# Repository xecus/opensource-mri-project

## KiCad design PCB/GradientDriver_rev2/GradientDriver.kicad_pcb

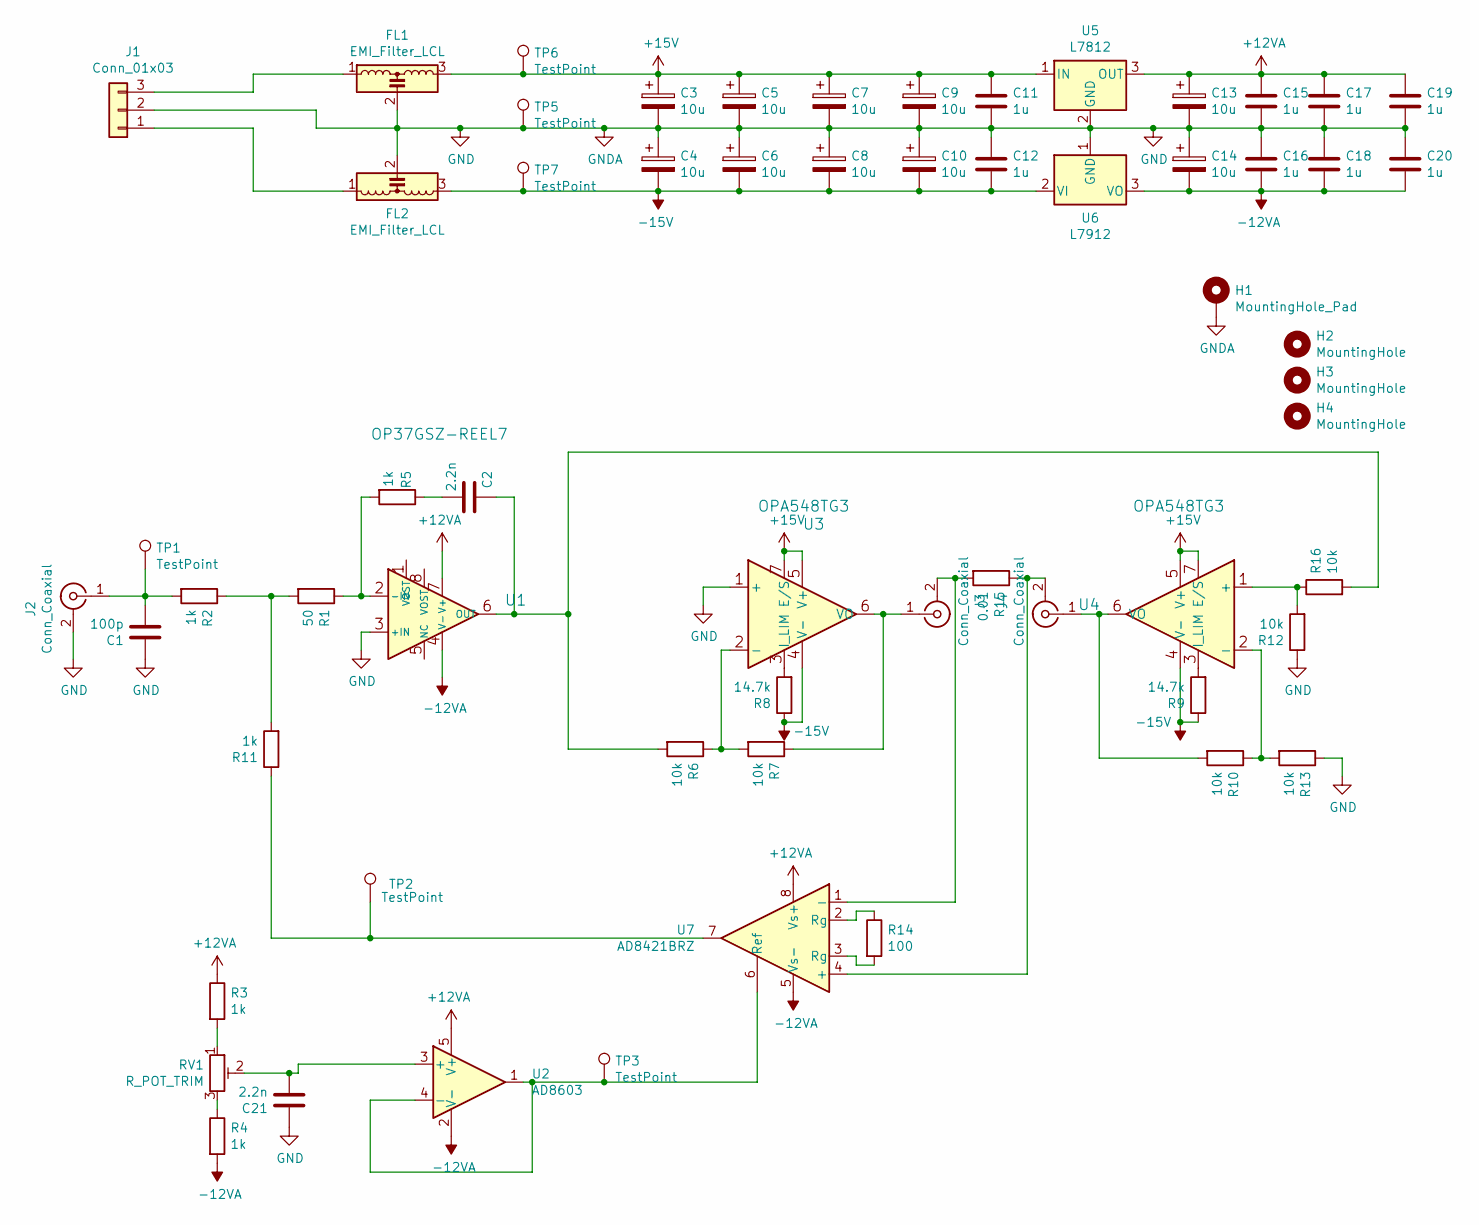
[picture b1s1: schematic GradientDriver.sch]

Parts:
C1: 100p; C_0603_1608Metric_Pad1.05x0.95mm_HandSolder
C2, C21: 2.2n; C_0603_1608Metric_Pad1.05x0.95mm_HandSolder
C3, C4, C5, C6, C7, C8, C9, C10, C13, C14: 10u; C_Elec_5x5.8
C11, C12, C15, C16, C17, C18, C19, C20: 1u; C_0603_1608Metric_Pad1.05x0.95mm_HandSolder
FL1, FL2: EMI_Filter_LCL; EMI_Filter_2606
H1: MountingHole_Pad; MountingHole_3.2mm_M3_Pad_Via
H2, H3, H4: MountingHole; MountingHole_3.2mm_M3_Pad_Via
J1: Conn_01x03; JST_XH_S3B-XH-A-1_1x03_P2.50mm_Horizontal
J2, J3, J4: Conn_Coaxial; SMA_Samtec_SMA-J-P-X-ST-EM1_EdgeMount
R1: 50; R_0603_1608Metric_Pad1.05x0.95mm_HandSolder
R2, R3, R4, R5, R11: 1k; R_0603_1608Metric_Pad1.05x0.95mm_HandSolder
R6, R7, R10, R12, R13, R16: 10k; R_0603_1608Metric_Pad1.05x0.95mm_HandSolder
R8, R9: 14.7k; R_0603_1608Metric_Pad1.05x0.95mm_HandSolder
R14: 100; R_0603_1608Metric_Pad1.05x0.95mm_HandSolder
R15: 0.01; R_2512_6332Metric_Pad1.52x3.35mm_HandSolder
RV1: R_POT_TRIM; Potentiometer_Bourns_3269W_Vertical
TP1, TP2, TP3, TP5, TP6, TP7: TestPoint; HK-1-G
U1: OP37GSZ-REEL7; SSOP-8_3.9x5.05mm_P1.27mm
U2: AD8603; TSOT-23-5
U3, U4: OPA548TG3
U5: L7812; TO-252-3_TabPin4
U6: L7912; TO-252-3_TabPin4
U7: AD8421BRZ; SOIC-8-1EP_3.9x4.9mm_P1.27mm_EP2.29x3mm

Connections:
+12VA: C13.1, C15.1, C17.1, C19.1, R3.1, U1.7 (V+), U2.5 (V+), U5.3 (OUT), U7.8 (Vs+)
+15V: C3.1, C5.1, C7.1, C9.1, C11.1, FL1.3, TP6.1, U3.5 (V+), U3.7 (E/S), U4.5 (V+), U4.7 (E/S), U5.1 (IN)
-12VA: C14.2, C16.2, C18.2, C20.2, R4.2, U1.4 (V-), U2.2 (V-), U6.3 (VO), U7.5 (Vs-)
-15V: C4.2, C6.2, C8.2, C10.2, C12.2, FL2.3, R8.1, R9.1, TP7.1, U3.4 (V-), U4.4 (V-), U6.2 (VI), U6.4
GND: C1.1, C3.2, C4.1, C5.2, C6.1, C7.2, C8.1, C9.2, C10.1, C11.2, C12.1, C13.2, C14.1, C15.2, C16.1, C17.2, C18.1, C19.2, C20.1, C21.1, FL1.2, FL2.2, H1.1, J1.2, J2.2 (Ext), R12.1, R13.1, TP5.1, U1.3 (+IN), U3.1 (+), U5.2 (GND), U6.1 (GND)
unnamed: C1.2, J2.1 (In), R2.2, TP1.1
unnamed: C2.1, R6.2, R16.2, U1.6 (OUT)
unnamed: C2.2, R5.1
unnamed: C21.2, RV1.2, U2.3 (+)
unnamed: FL1.1, J1.3
unnamed: FL2.1, J1.1
unnamed: J3.1 (In), R7.1, U3.6 (VO)
unnamed: J3.2 (Ext), R15.2, U7.1 (-)
unnamed: J4.1 (In), R10.2, U4.6 (VO)
unnamed: J4.2 (Ext), R15.1, U7.4 (+)
unnamed: R1.1, R5.2, U1.2 (-IN)
unnamed: R1.2, R2.1, R11.2
unnamed: R3.2, RV1.1
unnamed: R4.1, RV1.3
unnamed: R6.1, R7.2, U3.2 (-)
unnamed: R8.2, U3.3 (I_LIM)
unnamed: R9.2, U4.3 (I_LIM)
unnamed: R10.1, R13.2, U4.2 (-)
unnamed: R11.1, TP2.1, U7.7
unnamed: R12.2, R16.1, U4.1 (+)
unnamed: R14.1, U7.2 (Rg)
unnamed: R14.2, U7.3 (Rg)
unnamed: TP3.1, U2.1, U2.4 (-), U7.6 (Ref)

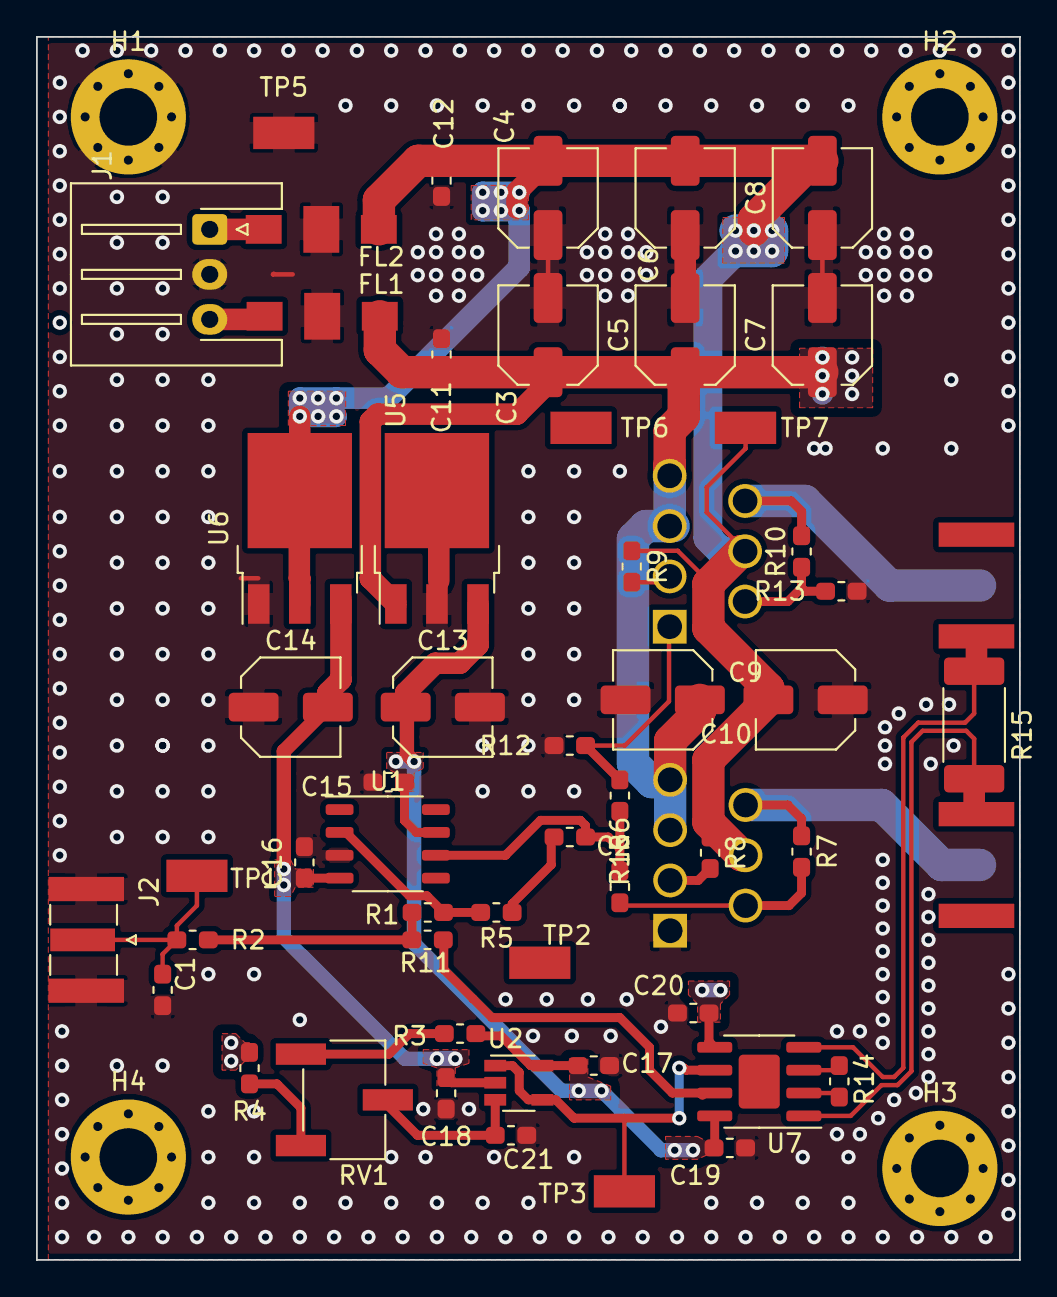
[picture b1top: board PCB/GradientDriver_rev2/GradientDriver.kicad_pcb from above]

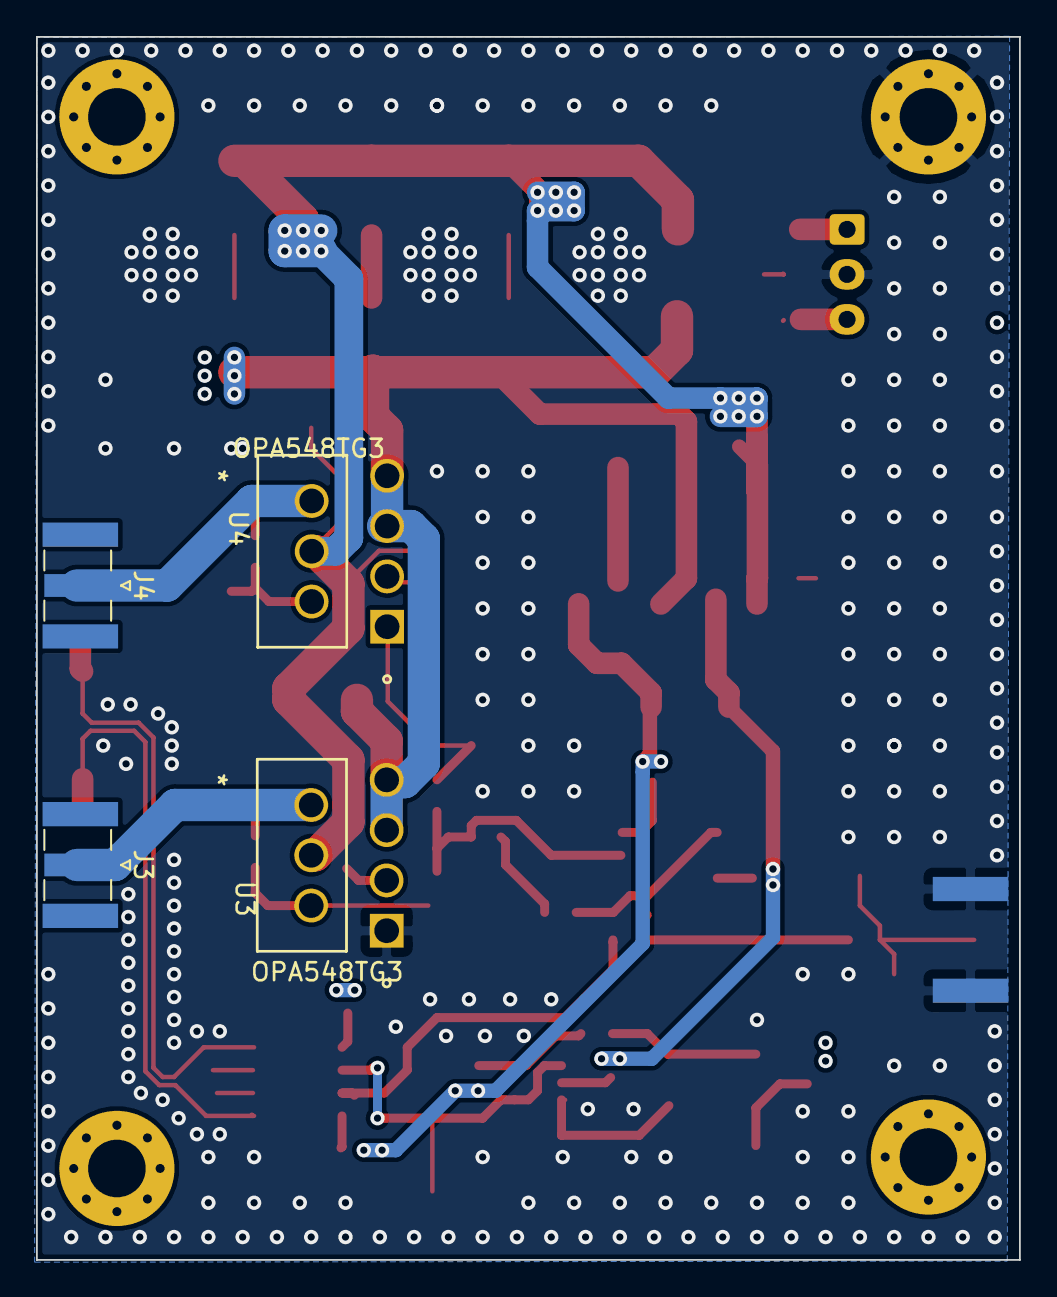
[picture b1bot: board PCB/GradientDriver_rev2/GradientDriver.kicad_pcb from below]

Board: 4 copper layers, 54.6 x 67.9 mm, 61 parts (4 on the bottom side), 28 nets.

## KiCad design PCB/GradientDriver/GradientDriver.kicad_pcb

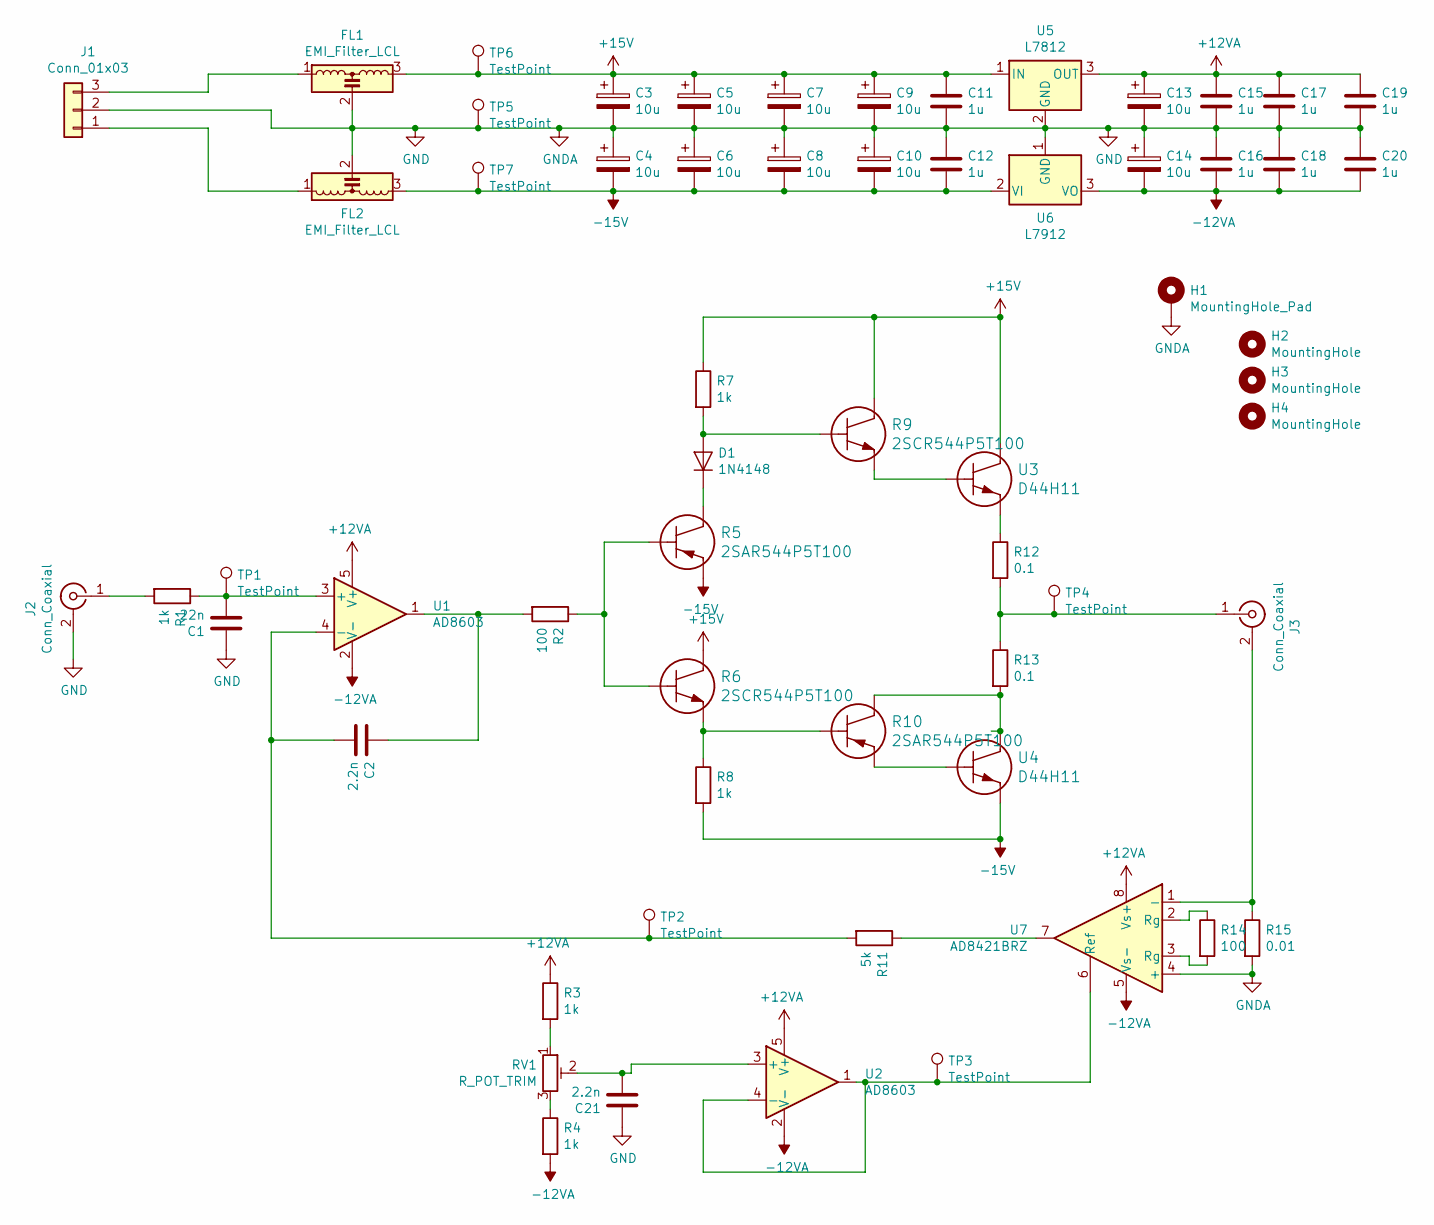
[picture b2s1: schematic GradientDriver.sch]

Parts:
C1: 22n; C_0603_1608Metric_Pad1.05x0.95mm_HandSolder
C2, C21: 2.2n; C_0603_1608Metric_Pad1.05x0.95mm_HandSolder
C3, C4, C5, C6, C7, C8, C9, C10, C13, C14: 10u; C_Elec_5x5.8
C11, C12, C15, C16, C17, C18, C19, C20: 1u; C_0603_1608Metric_Pad1.05x0.95mm_HandSolder
D1: 1N4148; D_SOD-323_HandSoldering
FL1, FL2: EMI_Filter_LCL; EMI_Filter_2606
H1: MountingHole_Pad; MountingHole_3.2mm_M3_Pad_Via
H2, H3, H4: MountingHole; MountingHole_3.2mm_M3_Pad_Via
J1: Conn_01x03; JST_XH_S3B-XH-A-1_1x03_P2.50mm_Horizontal
J2, J3: Conn_Coaxial; SMA_Samtec_SMA-J-P-X-ST-EM1_EdgeMount
R1, R3, R4, R7, R8: 1k; R_0603_1608Metric_Pad1.05x0.95mm_HandSolder
R2, R14: 100; R_0603_1608Metric_Pad1.05x0.95mm_HandSolder
R5, R10: 2SAR544P5T100; SOT-89-3_Handsoldering
R6, R9: 2SCR544P5T100; SOT-89-3_Handsoldering
R11: 5k; R_0603_1608Metric_Pad1.05x0.95mm_HandSolder
R12, R13: 0.1; TLRH3APTTER100F
R15: 0.01; R_2512_6332Metric_Pad1.52x3.35mm_HandSolder
RV1: R_POT_TRIM; Potentiometer_Bourns_3269W_Vertical
TP1, TP2, TP3, TP4, TP5, TP6, TP7: TestPoint; HK-1-G
U1, U2: AD8603; TSOT-23-5
U3, U4: D44H11
U5: L7812; TO-252-3_TabPin4
U6: L7912; TO-252-3_TabPin4
U7: AD8421BRZ; SOIC-8-1EP_3.9x4.9mm_P1.27mm_EP2.29x3mm

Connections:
+12VA: C13.1, C15.1, C17.1, C19.1, R3.1, U1.5 (V+), U2.5 (V+), U5.3 (OUT), U7.8 (Vs+)
+15V: C3.1, C5.1, C7.1, C9.1, C11.1, FL1.3, R6.2, R7.1, R9.2, TP6.1, U3.2 (C), U5.1 (IN)
-12VA: C14.2, C16.2, C18.2, C20.2, R4.2, U1.2 (V-), U2.2 (V-), U6.3 (VO), U7.5 (Vs-)
-15V: C4.2, C6.2, C8.2, C10.2, C12.2, FL2.3, R5.3, R8.2, TP7.1, U4.3 (E), U6.2 (VI), U6.4
GND: C1.1, C3.2, C4.1, C5.2, C6.1, C7.2, C8.1, C9.2, C10.1, C11.2, C12.1, C13.2, C14.1, C15.2, C16.1, C17.2, C18.1, C19.2, C20.1, C21.1, FL1.2, FL2.2, H1.1, J1.2, J2.2 (Ext), R15.2, TP5.1, U5.2 (GND), U5.4, U6.1 (GND), U7.4 (+)
unnamed: C1.2, R1.1, TP1.1, U1.3 (+)
unnamed: C2.1, R2.2, U1.1
unnamed: C2.2, R11.2, TP2.1, U1.4 (-)
unnamed: C21.2, RV1.2, U2.3 (+)
unnamed: D1.1 (K), R5.2
unnamed: D1.2 (A), R7.2, R9.1
unnamed: FL1.1, J1.3
unnamed: FL2.1, J1.1
unnamed: J2.1 (In), R1.2
unnamed: J3.1 (In), R12.2, R13.1, TP4.1
unnamed: J3.2 (Ext), R15.1, U7.1 (-)
unnamed: R2.1, R5.1, R6.1
unnamed: R3.2, RV1.1
unnamed: R4.1, RV1.3
unnamed: R9.3, U3.1 (B)
unnamed: R6.3, R8.1, R10.1
unnamed: R10.2, R13.2, U4.2 (C)
unnamed: R10.3, U4.1 (B)
unnamed: R11.1, U7.7
unnamed: R12.1, U3.3 (E)
unnamed: R14.1, U7.2 (Rg)
unnamed: R14.2, U7.3 (Rg)
unnamed: TP3.1, U2.1, U2.4 (-), U7.6 (Ref)

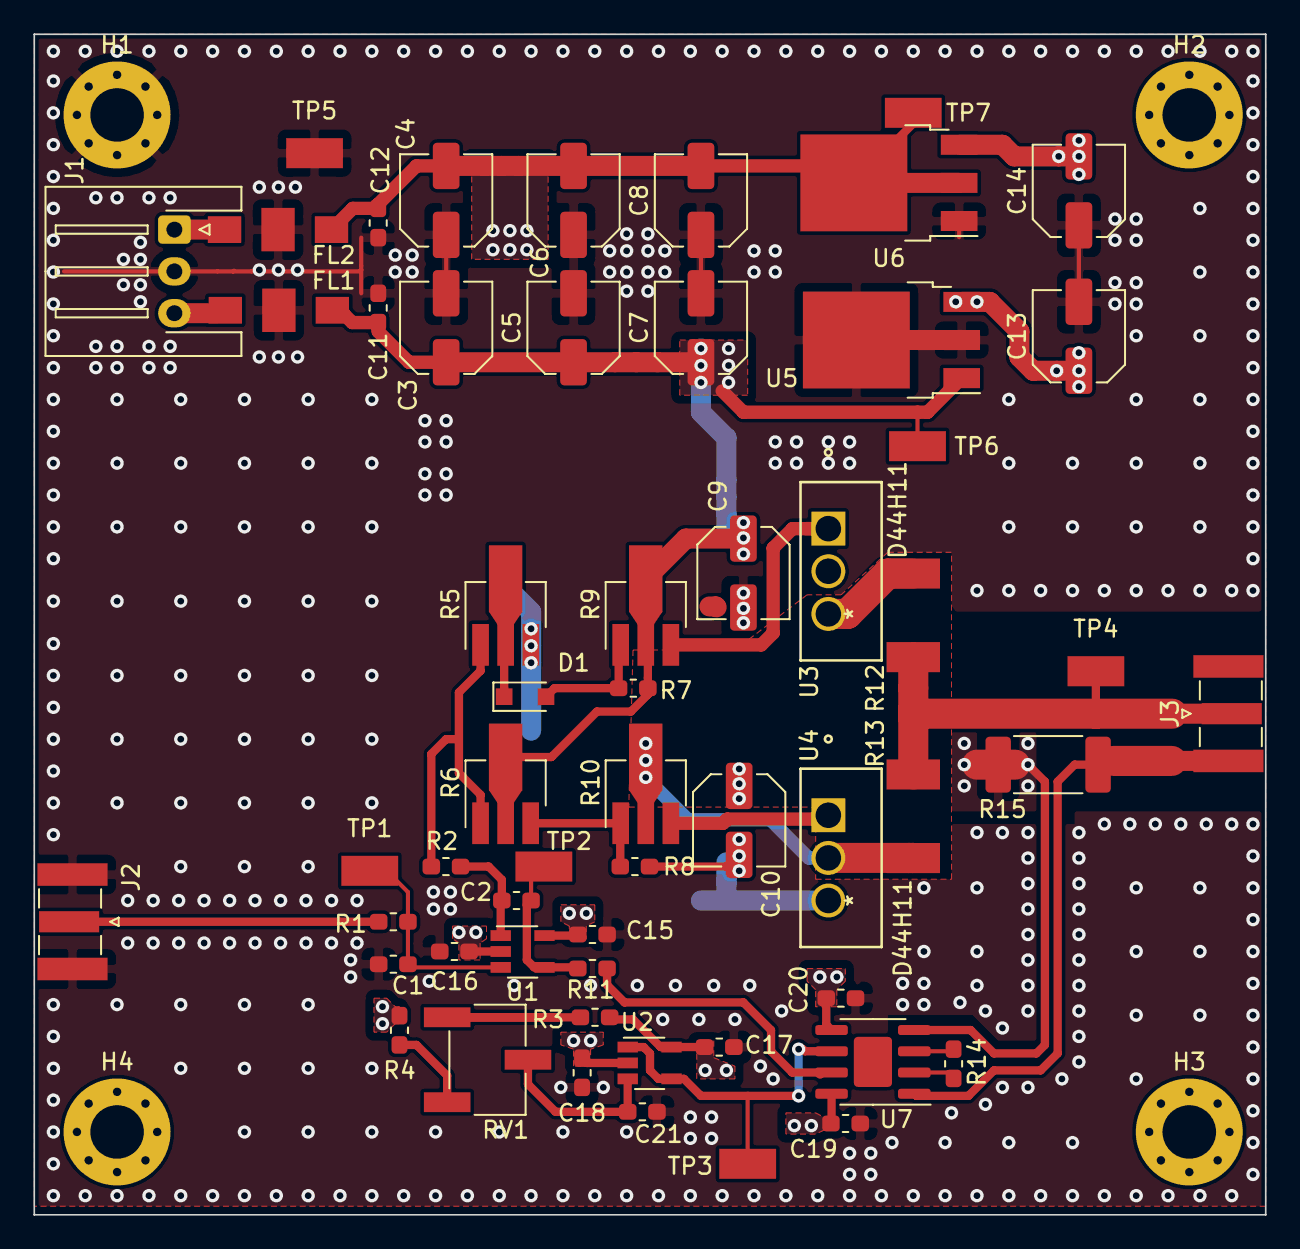
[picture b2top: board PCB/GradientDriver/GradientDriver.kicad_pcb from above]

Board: 4 copper layers, 73.7 x 70.6 mm, 61 parts (0 on the bottom side), 28 nets.

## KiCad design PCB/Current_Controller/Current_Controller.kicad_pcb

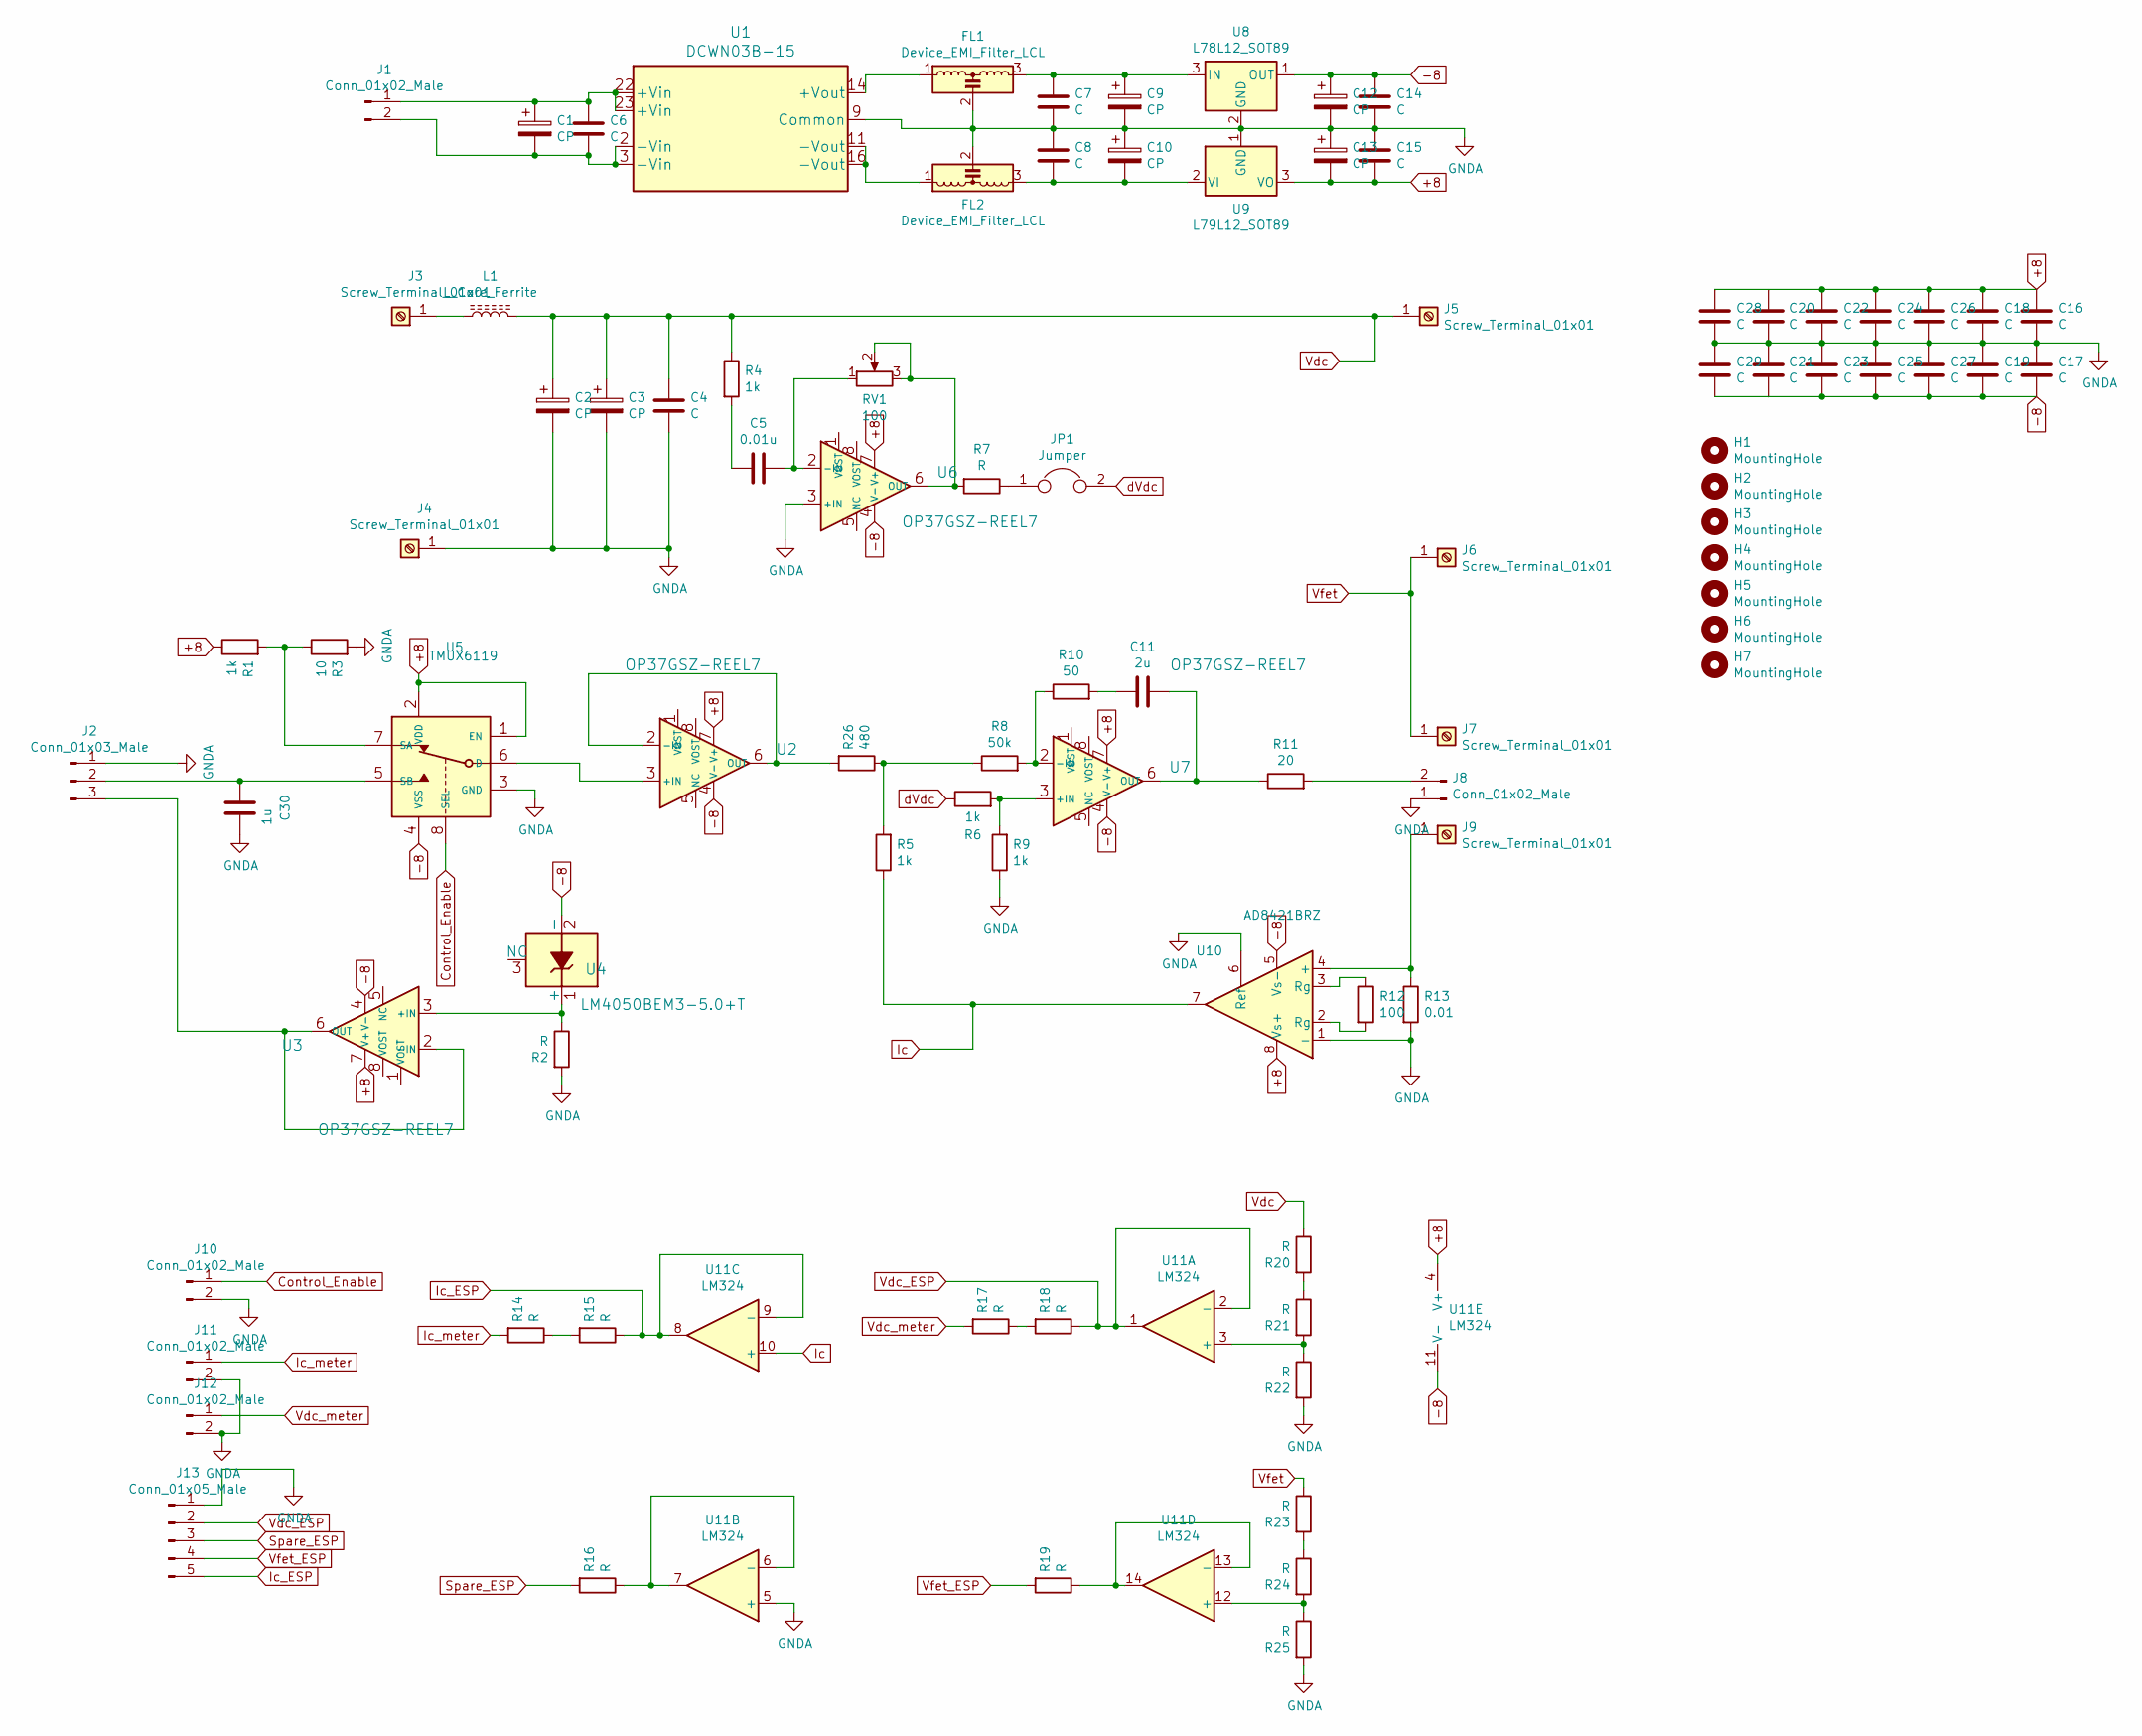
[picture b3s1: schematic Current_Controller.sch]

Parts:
C1, C9, C10, C12, C13: CP; CP_Elec_5x5.8
C2, C3: CP; CP_Radial_D30.0mm_P10.00mm_SnapIn
C4: C; C_Rect_L10.3mm_W5.7mm_P7.50mm_MKS4
C5: 0.01u; C_0603_1608Metric
C6, C7, C8, C14, C15, C16, C17, C18, C19, C20, C21, C22, C23, C24, C25, C26, C27, C28, C29: C; C_0603_1608Metric
C11: 2u; C_0603_1608Metric
C30: 1u; C_0603_1608Metric
FL1, FL2: Device_EMI_Filter_LCL; EMI_Filter_2606
H1, H2, H3, H4, H5, H6, H7: MountingHole; MountingHole_3.2mm_M3_Pad_Via
J1, J8, J10, J11, J12: Conn_01x02_Male; JST_XH_B2B-XH-AM_1x02_P2.50mm_Vertical
J2: Conn_01x03_Male; JST_XH_B3B-XH-AM_1x03_P2.50mm_Vertical
J3, J4, J5, J6, J7, J9: Screw_Terminal_01x01; keystone_7698
J13: Conn_01x05_Male; JST_XH_B5B-XH-AM_1x05_P2.50mm_Vertical
JP1: Jumper; PinHeader_1x02_P2.54mm_Vertical
L1: L_Core_Ferrite; L_250uH2
R1, R4, R5, R6, R9: 1k; R_0603_1608Metric
R2, R7, R14, R15, R16, R17, R18, R19, R20, R21, R22, R23, R24, R25: R; R_0603_1608Metric
R3: 10; R_0603_1608Metric
R8: 50k; R_0603_1608Metric
R10: 50; R_0603_1608Metric
R11: 20; R_0603_1608Metric
R12: 100; R_0603_1608Metric
R13: 0.01; GMR100HTBFA10L0
R26: 480; R_0603_1608Metric
RV1: 100; Potentiometer_Bourns_3269W_Vertical
U1: DCWN03B-15; DCWN03B-12
U2, U3, U6, U7: OP37GSZ-REEL7; SOIC-8_3.9x4.9mm_P1.27mm
U4: LM4050BEM3-5.0+T; LM4050QBEM3-8.2&slash_NOPB
U5: TMUX6119; SOT-23-8
U8: L78L12_SOT89; SOT-89-3
U9: L79L12_SOT89; SOT-89-3
U10: AD8421BRZ; SOIC-8_3.9x4.9mm_P1.27mm
U11: LM324; TSSOP-14_4.4x5mm_P0.65mm

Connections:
+8: C13.2, C15.1, C16.2, C18.2, C20.2, C22.2, C24.2, C26.2, C28.2, R1.1, U2.7 (V+), U3.7 (V+), U5.1 (EN), U5.2 (VDD), U6.7 (V+), U7.7 (V+), U9.3 (VO), U10.8 (Vs+), U11.4 (V+)
-8: C12.1, C14.2, C17.1, C19.1, C21.1, C23.1, C25.1, C27.1, C29.1, U2.4 (V-), U3.4 (V-), U4.2 (-), U5.4 (VSS), U6.4 (V-), U7.4 (V-), U8.1 (OUT), U10.5 (Vs-), U11.11 (V-)
Control_Enable: J10.1, U5.8 (SEL)
GNDA: C2.2, C3.2, C4.1, C7.1, C8.2, C9.2, C10.1, C12.2, C13.1, C14.1, C15.2, C16.1, C17.2, C18.1, C19.2, C20.1, C21.2, C22.1, C23.2, C24.1, C25.2, C26.1, C27.2, C28.1, C29.2, C30.1, FL1.2, FL2.2, J2.1, J4.1, J8.1, J10.2, J11.2, J12.2, J13.1, R2.2, R3.2, R9.1, R13.2, R22.2, R25.2, U1.9 (Common), U5.3 (GND), U6.3 (+IN), U8.2 (GND), U9.1 (GND), U10.1 (-), U10.6 (Ref), U11.5 (+)
Ic: R5.1, U10.7, U11.10 (+)
Ic_ESP: J13.5, R15.1, U11.8, U11.9 (-)
Ic_meter: J11.1, R14.2
unnamed: C1.1, C6.2, J1.1, U1.22 (+Vin), U1.23 (+Vin)
unnamed: C1.2, C6.1, J1.2, U1.2 (-Vin), U1.3 (-Vin)
unnamed: C5.1, RV1.1, U6.2 (-IN)
unnamed: C5.2, R4.2
unnamed: C7.2, C9.1, FL1.3, U8.3 (IN)
unnamed: C8.1, C10.2, FL2.3, U9.2 (VI)
unnamed: C11.1, R11.1, U7.6 (OUT)
unnamed: C11.2, R10.2
unnamed: C30.2, J2.2, U5.5 (SB)
unnamed: FL1.1, U1.14 (+Vout)
unnamed: FL2.1, U1.11 (-Vout), U1.16 (-Vout)
unnamed: J2.3, U3.2 (-IN), U3.6 (OUT)
unnamed: J3.1, L1.1
unnamed: J8.2, R11.2
unnamed: J9.1, R13.1, U10.4 (+)
unnamed: JP1.1, R7.1
unnamed: R1.2, R3.1, U5.7 (SA)
unnamed: R2.1, U3.3 (+IN), U4.1 (+)
unnamed: R6.2, R9.2, U7.3 (+IN)
unnamed: R7.2, RV1.2, RV1.3, U6.6 (OUT)
unnamed: R8.2, R10.1, U7.2 (-IN)
unnamed: R12.1, U10.3 (Rg)
unnamed: R12.2, U10.2 (Rg)
unnamed: R14.1, R15.2
unnamed: R16.1, U11.6 (-), U11.7
unnamed: R17.1, R18.2
unnamed: R19.1, U11.13 (-), U11.14
unnamed: R20.2, R21.1
unnamed: R21.2, R22.1, U11.3 (+)
unnamed: R23.2, R24.1
unnamed: R24.2, R25.1, U11.12 (+)
unnamed: R5.2, R8.1, R26.1
unnamed: R26.2, U2.2 (-IN), U2.6 (OUT)
unnamed: U2.3 (+IN), U5.6 (D)
Spare_ESP: J13.3, R16.2
Vdc: C2.1, C3.1, C4.2, J5.1, L1.2, R4.1, R20.1
Vdc_ESP: J13.2, R18.1, U11.1, U11.2 (-)
Vdc_meter: J12.1, R17.2
Vfet: J6.1, J7.1, R23.1
Vfet_ESP: J13.4, R19.2
dVdc: JP1.2, R6.1

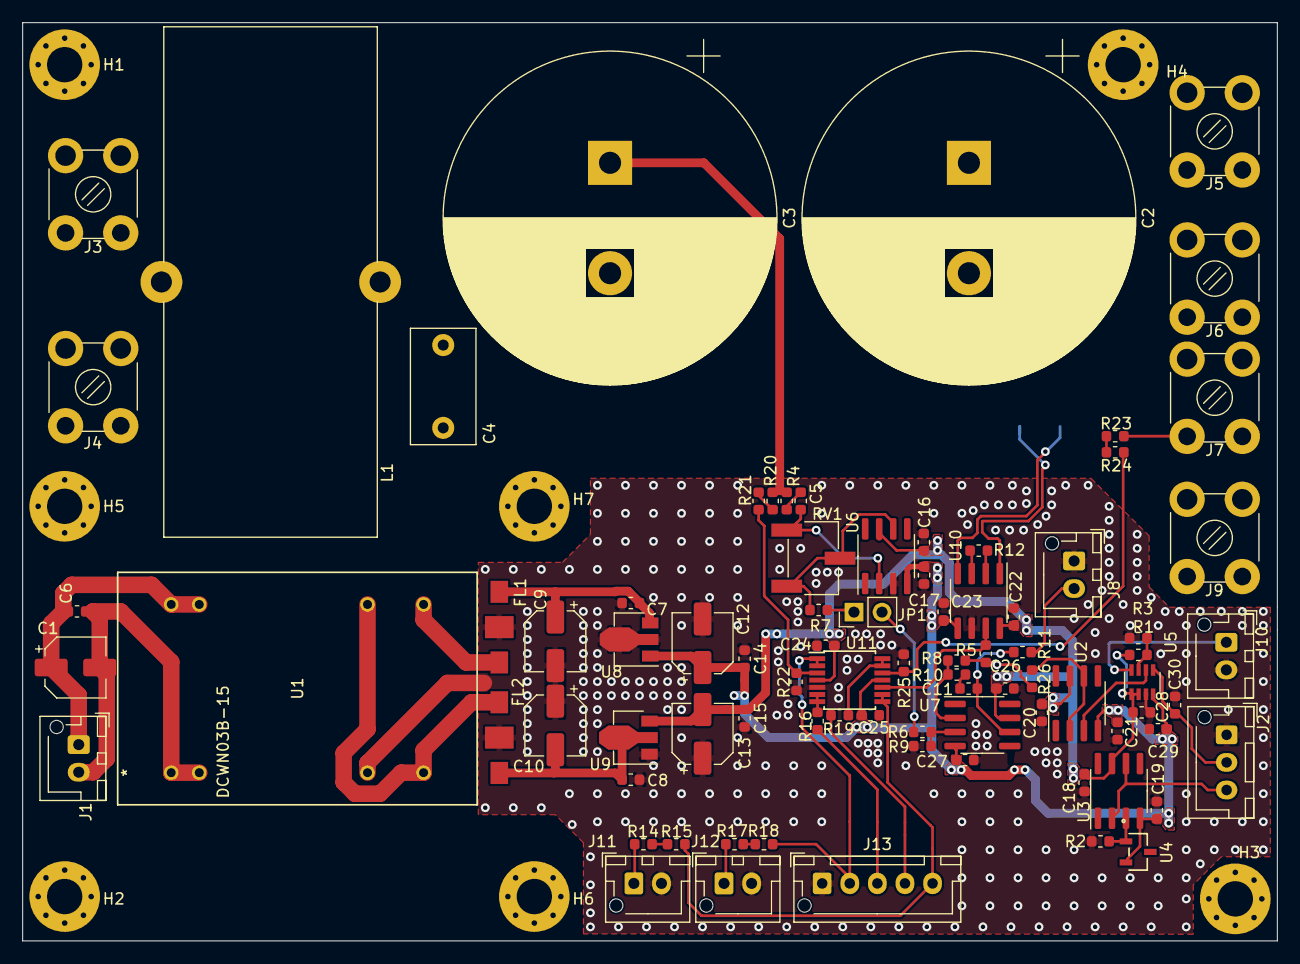
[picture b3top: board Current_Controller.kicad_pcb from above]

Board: 2 copper layers, 113.7 x 83.2 mm, 92 parts (1 on the bottom side), 48 nets.

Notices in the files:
parts and their libraries:
Copyright 2016 Accelerated Designs. All rights reserved.
